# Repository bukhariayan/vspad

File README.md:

# vspad
This is my first PCB project. It is a macropad that I will use when coding with VSCode in order to make it a more efficient and effective experience. I haven't yet decided exactly what command each key will do, so the code may be edited in the future.

---

## Specifications

BOM:
* 6x cherry MX switches
* 2x SK6812 MINI LEDs
* 1x XIAO RP2040
* 1x EC11 rotary encoder
* 6x Blank DSA Keycaps
* 4x M3x16 Bolt
* 4x M3 Heatset

---
## Schematic

---

## PCB

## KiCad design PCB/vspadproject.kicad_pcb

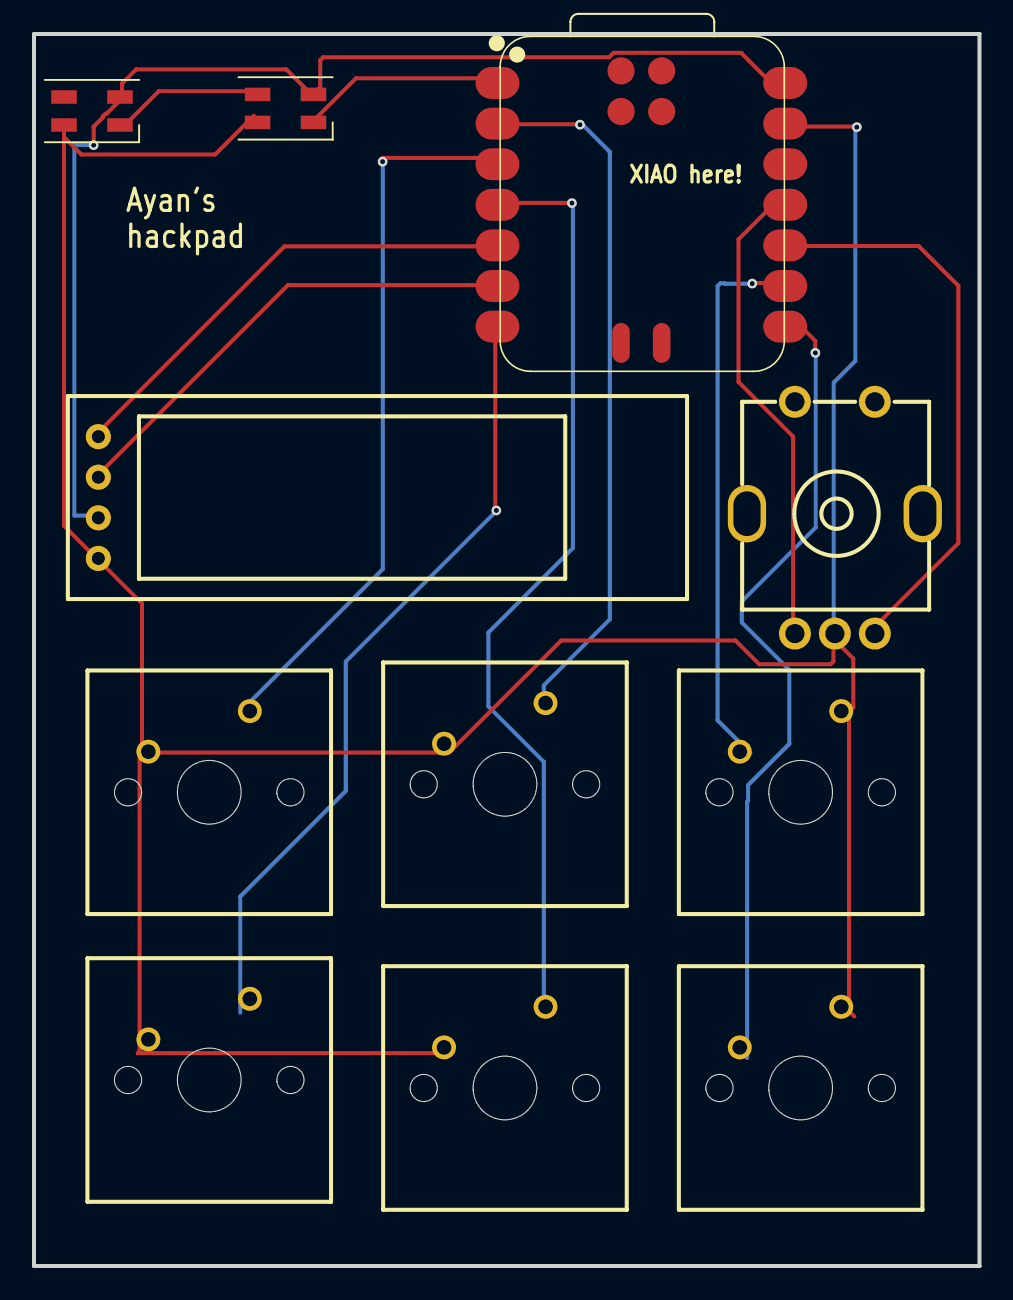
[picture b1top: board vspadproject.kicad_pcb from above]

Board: 2 copper layers, 59.2 x 77.1 mm, 11 parts (0 on the bottom side), 14 nets.

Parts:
D1, D2: LED Matrix - 96 well{colon}LED_SK6812MINI_PLCC4_3.5x3.5mm_P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
OLED1: I2C OLED 0.91
RP2: XIAO-RP2040-SMD
SW1: SW-TH_EC111XXXX
U2, U3, U4, U5, U6, U7: CHERRY MX KEYSWITCH

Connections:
$1N899: D1.1, D2.3
$1N1328: D1.3, RP2.1
$1N1348: OLED1.4, RP2.5
$1N1360: OLED1.3, RP2.6
$1N1796: RP2.2, U2.2
$1N1801: RP2.3, U3.2
$1N1814: RP2.7, U6.2
$1N1909: RP2.11, SW1.A
$1N1915: RP2.10, SW1.B
$1N2016: RP2.4, U5.2
$1N3030: RP2.9, U4.1
$1N3062: RP2.8, U7.1
+5V: D1.4, D2.4, OLED1.2, RP2.14
GND: D1.2, D2.2, OLED1.1, RP2.13, SW1.C, U2.1, U3.1, U4.2, U5.1, U6.1, U7.2

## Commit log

2026-01-06 Add code, pcb, and 3D files to the repository
2026-01-06 Update README with project specifications and BOM
    Added specifications and BOM for the macropad project.
2026-01-06 Add images of the schematic, PCB, and 3D model
2026-01-06 Revise README and add schematic and PCB sections
    Updated project description and added schematic and PCB sections.
2026-01-06 Add necessary files for PCB and 3D model that were missing previously
